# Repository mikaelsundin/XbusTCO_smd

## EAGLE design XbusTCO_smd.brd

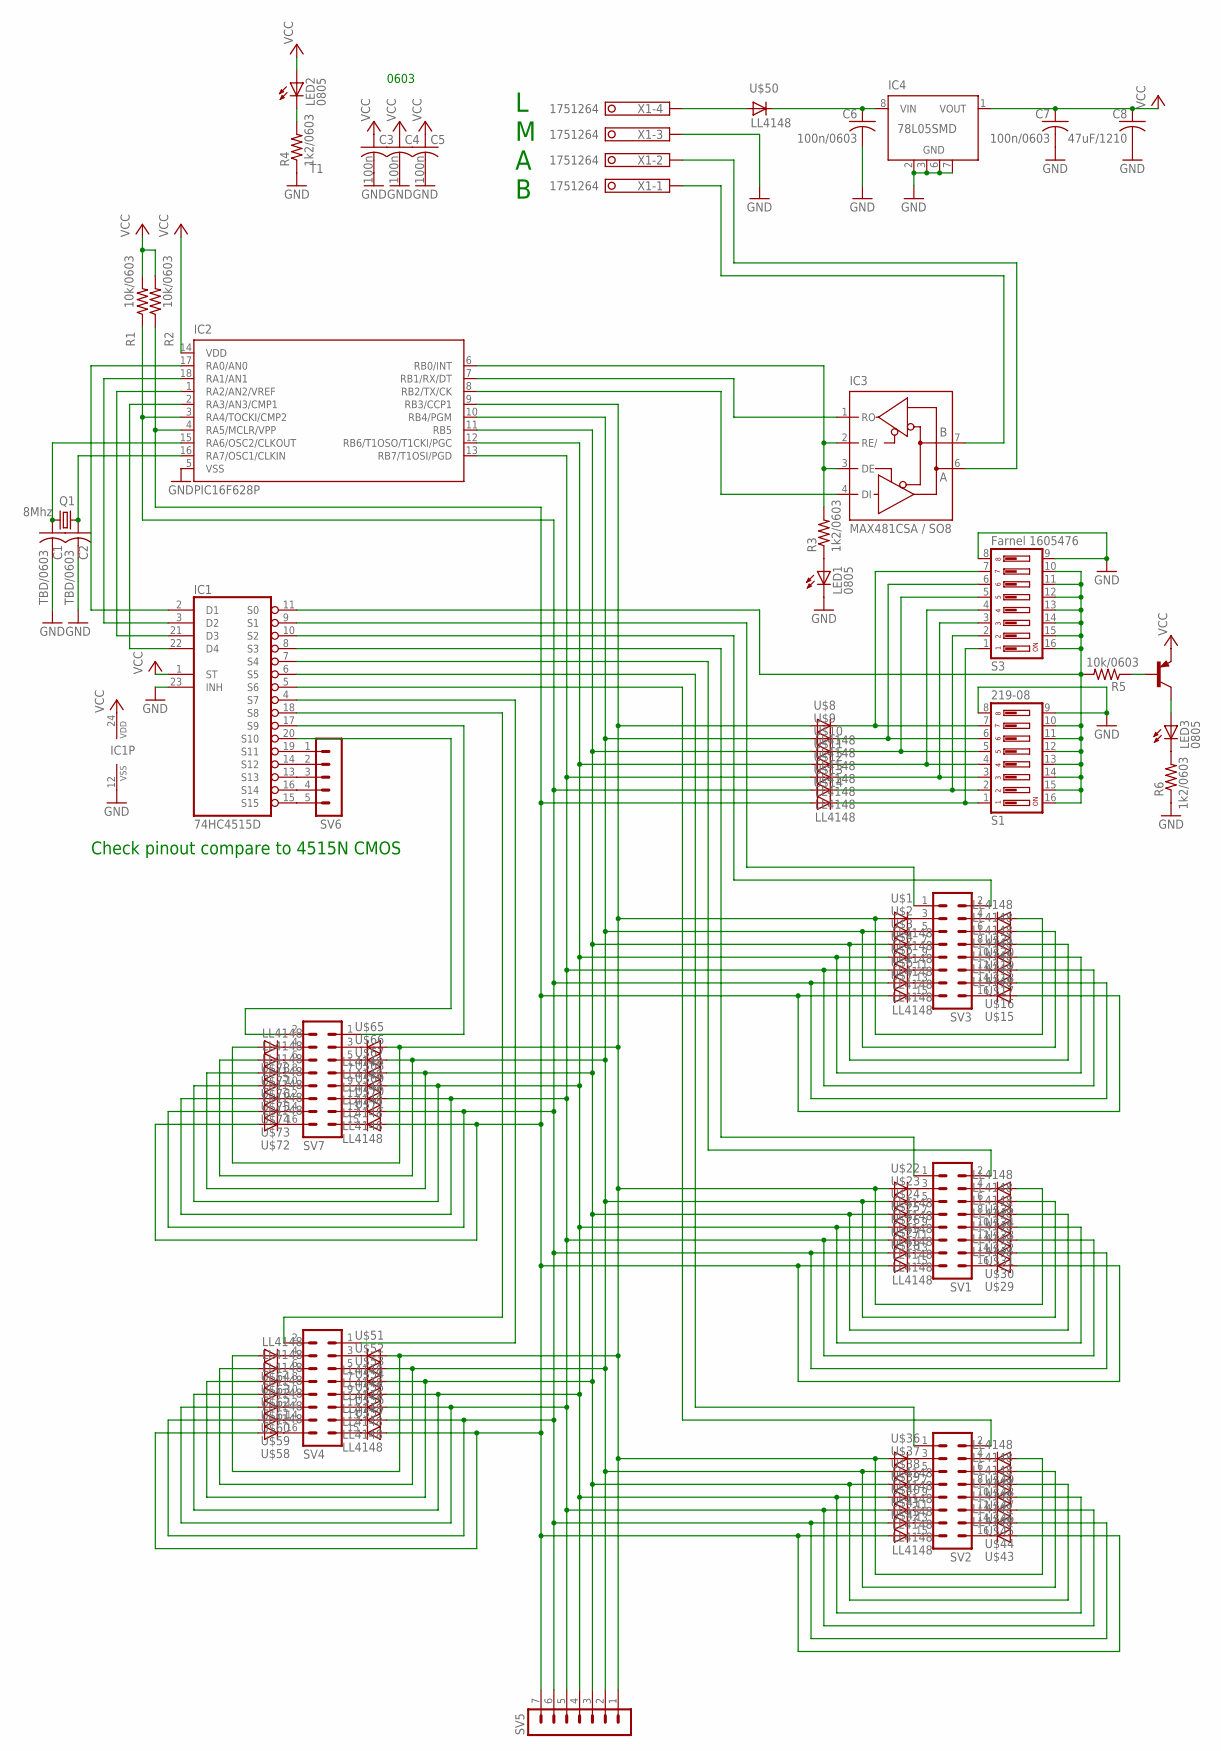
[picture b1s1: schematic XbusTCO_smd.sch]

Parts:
C1, C2: TBD/0603; C0603
C3, C4, C5: 100n; C0603
C6, C7: 100n/0603; C0603
C8: 47uF/1210; C1210
IC1: 74HC4515D; SO24W
IC2: PIC16F628P; DIL18
IC3: MAX481CSA / SO8; SO08
IC4: 78L05SMD; SO08
LED1, LED2, LED3: 0805; CHIPLED_0805
Q1: 8Mhz; HC49U70
R1, R2, R5: 10k/0603; R0603
R3, R4, R6: 1k2/0603; R0603
S1: 219-08; CTS-219-08
S3: Farnel 1605476; CTS-219-08J
SV1, SV2, SV3, SV4, SV7: MA08-2W
SV5: MA07-1
SV6: MA05-1
T1: BC857A-PNP-SOT23-BEC; SOT23-BEC
U$1, U$2, U$3, U$4, U$5, U$6, U$7, U$8, U$9, U$10, U$11, U$12, U$13, U$14, U$15, U$16, U$17, U$18, U$19, U$20, U$21, U$22, U$23, U$24, U$25, U$26, U$27, U$28, U$29, U$30, U$31, U$32, U$33, U$34, U$35, U$36, U$37, U$38, U$39, U$40, U$41, U$42, U$43, U$44, U$45, U$46, U$47, U$48, U$49, U$50, U$51, U$52, U$53, U$54, U$55, U$56, U$57, U$58, U$59, U$60, U$61, U$62, U$63, U$64, U$65, U$66, U$67, U$68, U$69, U$70, U$71, U$72, U$73, U$74, U$75, U$76, U$77, U$78: LL4148; MINIMELF
X1: 1751264

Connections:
GND: C1.2, C2.2, C3.2, C4.2, C5.2, C6.2, C7.2, C8.2, IC1.12 (VSS), IC1.23 (INH), IC2.5 (VSS), IC3.5 (GND), IC4.2 (GND), IC4.3 (GND), IC4.6 (GND), IC4.7 (GND), LED1.C, R4.1, R6.1, S1.8, S1.9, S3.8, S3.9, X1.3
unnamed: C1.1, IC2.15 (RA6/OSC2/CLKOUT), Q1.2
unnamed: C2.1, IC2.16 (RA7/OSC1/CLKIN), Q1.1
unnamed: IC1.2 (D1), IC2.17 (RA0/AN0)
unnamed: IC1.3 (D2), IC2.18 (RA1/AN1)
unnamed: IC1.21 (D3), IC2.1 (RA2/AN2/VREF)
unnamed: IC1.22 (D4), IC2.2 (RA3/AN3/CMP1)
unnamed: IC2.6 (RB0/INT), IC3.2 (RE/), IC3.3 (DE), R3.2
unnamed: IC2.8 (RB2/TX/CK), IC3.4 (DI)
unnamed: IC2.7 (RB1/RX/DT), IC3.1 (RO)
unnamed: IC2.9 (RB3/CCP1), SV5.1, U$1.A, U$8.A, U$21.A, U$22.A, U$35.A, U$36.A, U$49.A, U$51.A, U$64.A, U$65.A, U$78.A
unnamed: IC2.10 (RB4/PGM), SV5.2, U$2.A, U$9.A, U$20.A, U$23.A, U$34.A, U$37.A, U$48.A, U$52.A, U$63.A, U$66.A, U$77.A
unnamed: IC2.11 (RB5), SV5.3, U$3.A, U$10.A, U$19.A, U$24.A, U$33.A, U$38.A, U$47.A, U$53.A, U$62.A, U$67.A, U$76.A
unnamed: IC2.12 (RB6/T1OSO/T1CKI/PGC), SV5.4, U$4.A, U$11.A, U$18.A, U$25.A, U$32.A, U$39.A, U$46.A, U$54.A, U$61.A, U$68.A, U$75.A
unnamed: IC2.13 (RB7/T1OSI/PGD), SV5.5, U$5.A, U$12.A, U$17.A, U$26.A, U$31.A, U$40.A, U$45.A, U$55.A, U$60.A, U$69.A, U$74.A
unnamed: IC2.3 (RA4/TOCKI/CMP2), R1.1, SV5.6, U$6.A, U$13.A, U$16.A, U$27.A, U$30.A, U$41.A, U$44.A, U$56.A, U$59.A, U$70.A, U$73.A
unnamed: IC2.4 (RA5/MCLR/VPP), R2.1, SV5.7, U$7.A, U$14.A, U$15.A, U$28.A, U$29.A, U$42.A, U$43.A, U$57.A, U$58.A, U$71.A, U$72.A
unnamed: IC1.9 (S1), SV3.1
unnamed: IC1.10 (S2), SV3.2
unnamed: C6.1, IC4.8 (VIN), U$50.C
unnamed: U$50.A, X1.4
unnamed: IC1.6 (S5), SV2.1
unnamed: IC3.6 (A), X1.2
unnamed: SV3.3, U$1.C
unnamed: SV3.5, U$2.C
unnamed: SV3.7, U$3.C
unnamed: SV3.9, U$4.C
unnamed: SV3.11, U$5.C
unnamed: SV3.13, U$6.C
unnamed: SV3.15, U$7.C
unnamed: IC1.11 (S0), R5.2, S1.10, S1.11, S1.12, S1.13, S1.14, S1.15, S1.16, S3.10, S3.11, S3.12, S3.13, S3.14, S3.15, S3.16
unnamed: S1.7, S3.7, U$8.C
unnamed: S1.6, S3.6, U$9.C
unnamed: S1.5, S3.5, U$10.C
unnamed: S1.4, S3.4, U$11.C
unnamed: S1.3, S3.3, U$12.C
unnamed: S1.2, S3.2, U$13.C
unnamed: S1.1, S3.1, U$14.C
unnamed: SV3.16, U$15.C
unnamed: SV3.14, U$16.C
unnamed: SV3.12, U$17.C
unnamed: SV3.10, U$18.C
unnamed: SV3.8, U$19.C
unnamed: SV3.6, U$20.C
unnamed: SV3.4, U$21.C
unnamed: IC3.7 (B), X1.1
unnamed: LED2.C, R4.2
unnamed: LED1.A, R3.1
unnamed: R5.1, T1.B
unnamed: LED3.A, T1.C
unnamed: LED3.C, R6.2
unnamed: IC1.5 (S6), SV2.2
unnamed: IC1.8 (S3), SV1.1
unnamed: IC1.7 (S4), SV1.2
unnamed: SV1.3, U$22.C
unnamed: SV1.5, U$23.C
unnamed: SV1.7, U$24.C
unnamed: SV1.9, U$25.C
unnamed: SV1.11, U$26.C
unnamed: SV1.13, U$27.C
unnamed: SV1.15, U$28.C
unnamed: SV1.16, U$29.C
unnamed: SV1.14, U$30.C
unnamed: SV1.12, U$31.C
unnamed: SV1.10, U$32.C
unnamed: SV1.8, U$33.C
unnamed: SV1.6, U$34.C
unnamed: SV1.4, U$35.C
unnamed: SV2.3, U$36.C
unnamed: SV2.5, U$37.C
unnamed: SV2.7, U$38.C
unnamed: SV2.9, U$39.C
unnamed: SV2.11, U$40.C
unnamed: SV2.13, U$41.C
unnamed: SV2.15, U$42.C
unnamed: SV2.16, U$43.C
unnamed: SV2.14, U$44.C
unnamed: SV2.12, U$45.C
unnamed: SV2.10, U$46.C
unnamed: SV2.8, U$47.C
unnamed: SV2.6, U$48.C
unnamed: SV2.4, U$49.C
unnamed: IC1.4 (S7), SV4.1
unnamed: IC1.18 (S8), SV4.2
unnamed: IC1.17 (S9), SV7.1
unnamed: IC1.20 (S10), SV7.2
unnamed: IC1.19 (S11), SV6.1
unnamed: IC1.14 (S12), SV6.2
unnamed: IC1.13 (S13), SV6.3
unnamed: IC1.16 (S14), SV6.4
unnamed: IC1.15 (S15), SV6.5
unnamed: SV7.3, U$65.C
unnamed: SV7.5, U$66.C
unnamed: SV4.3, U$51.C
unnamed: SV4.5, U$52.C
unnamed: SV4.7, U$53.C
unnamed: SV4.9, U$54.C
unnamed: SV4.11, U$55.C
unnamed: SV4.13, U$56.C
unnamed: SV4.15, U$57.C
unnamed: SV4.16, U$58.C
unnamed: SV4.14, U$59.C
unnamed: SV4.12, U$60.C
unnamed: SV4.10, U$61.C
unnamed: SV4.8, U$62.C
unnamed: SV4.6, U$63.C
unnamed: SV4.4, U$64.C
unnamed: SV7.7, U$67.C
unnamed: SV7.9, U$68.C
unnamed: SV7.11, U$69.C
unnamed: SV7.13, U$70.C
unnamed: SV7.15, U$71.C
unnamed: SV7.16, U$72.C
unnamed: SV7.14, U$73.C
unnamed: SV7.12, U$74.C
unnamed: SV7.10, U$75.C
unnamed: SV7.8, U$76.C
unnamed: SV7.6, U$77.C
unnamed: SV7.4, U$78.C
VCC: C3.1, C4.1, C5.1, C7.1, C8.1, IC1.1 (ST), IC1.24 (VDD), IC2.14 (VDD), IC3.8 (VCC), IC4.1 (VOUT), LED2.A, R1.2, R2.2, T1.E

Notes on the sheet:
Check pinout compare to 4515N CMOS
L M A B
0603

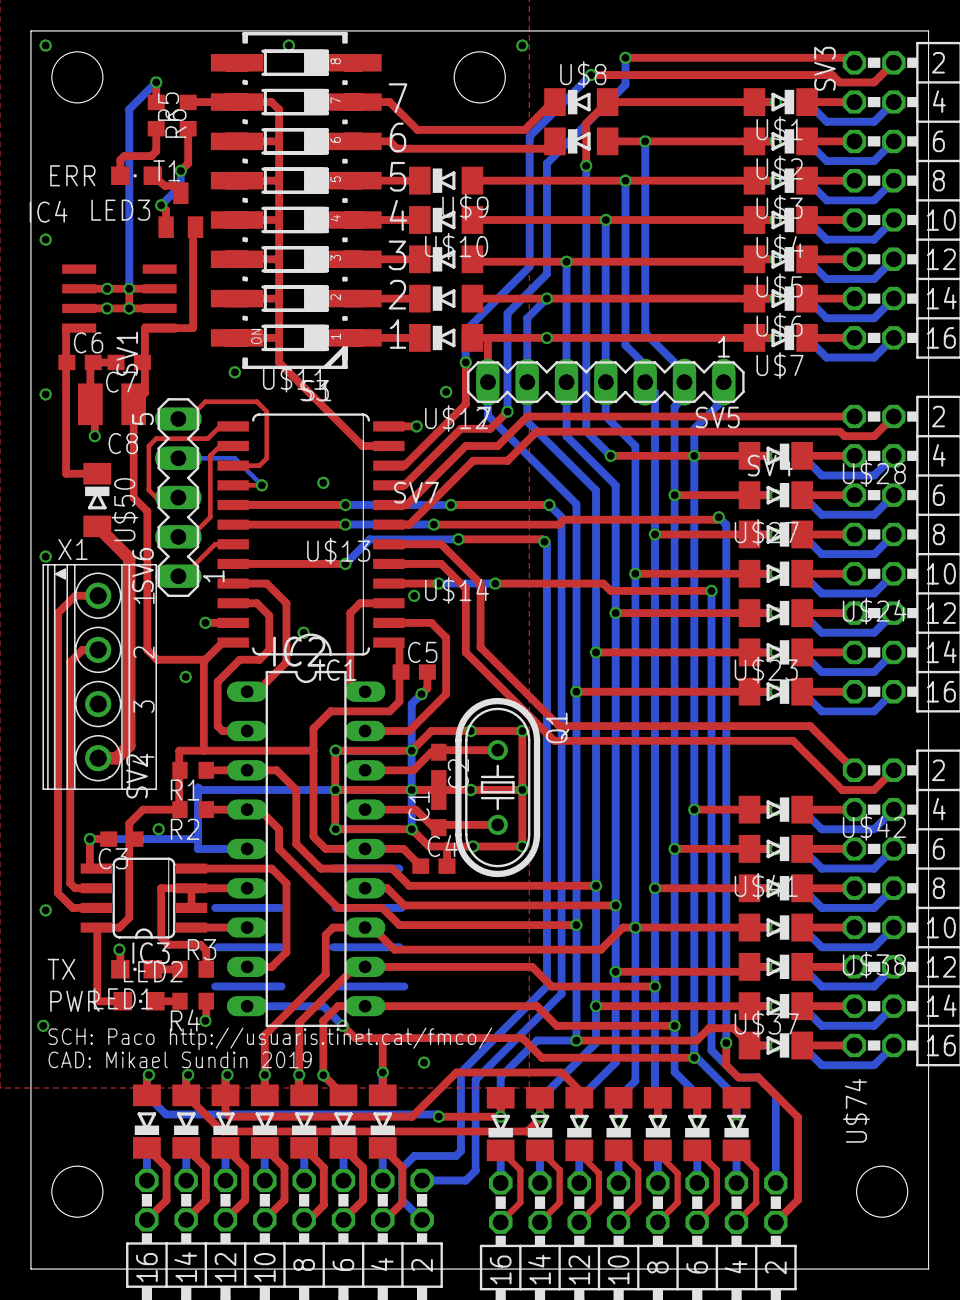
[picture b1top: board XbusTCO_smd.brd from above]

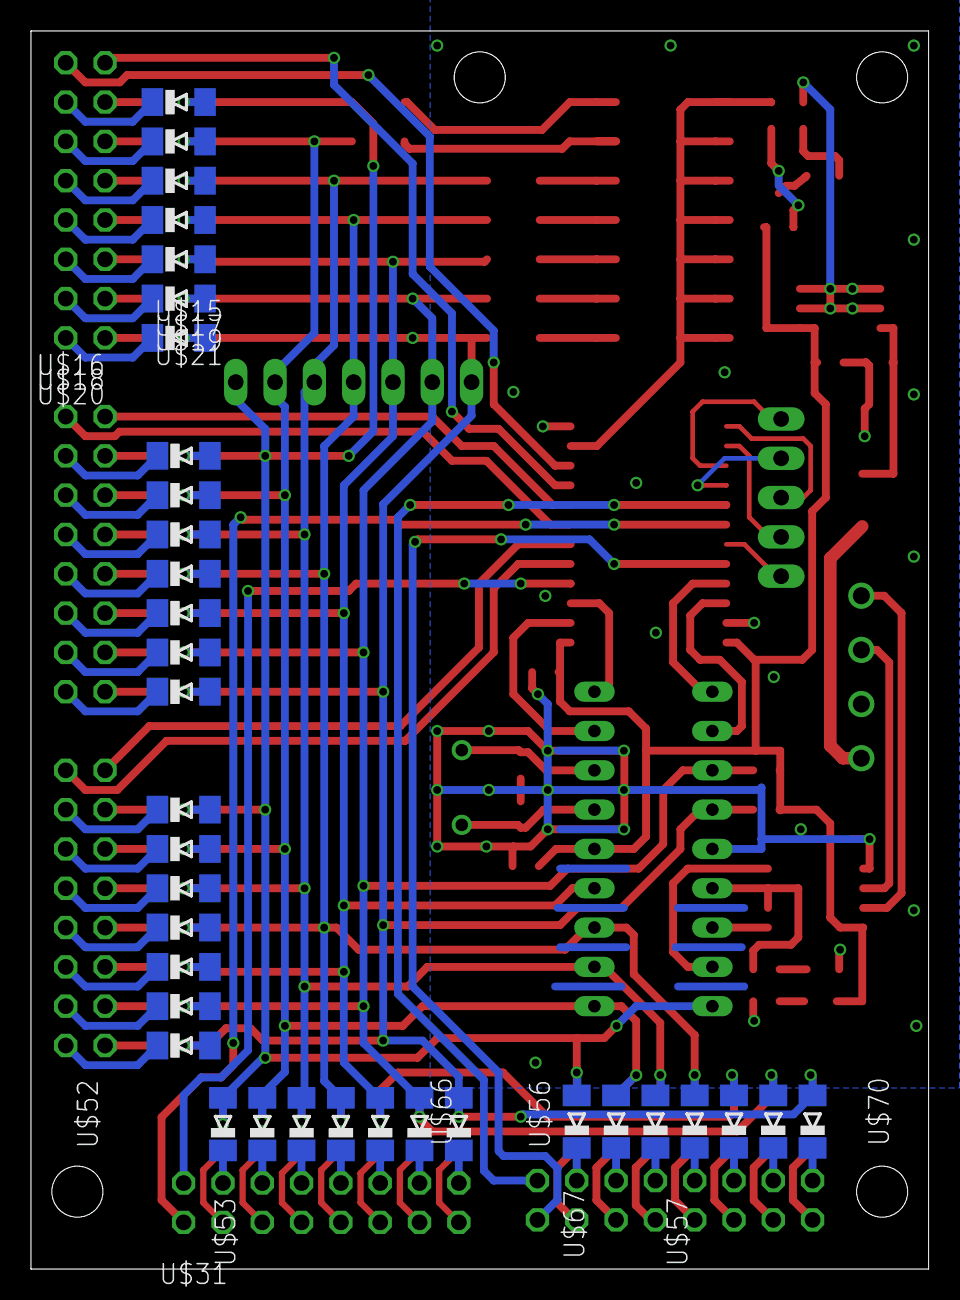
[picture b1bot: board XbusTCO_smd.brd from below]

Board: 2 copper layers, 58.0 x 80.0 mm, 111 parts (35 on the bottom side), 120 nets.

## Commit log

2019-05-26 PCB and schematic created, not verified.
2019-05-26 Updated DIL switch pinout.
2019-05-28 Added 2 more connectors.
2019-06-01 Added pdf files, added smd component size in value field.
